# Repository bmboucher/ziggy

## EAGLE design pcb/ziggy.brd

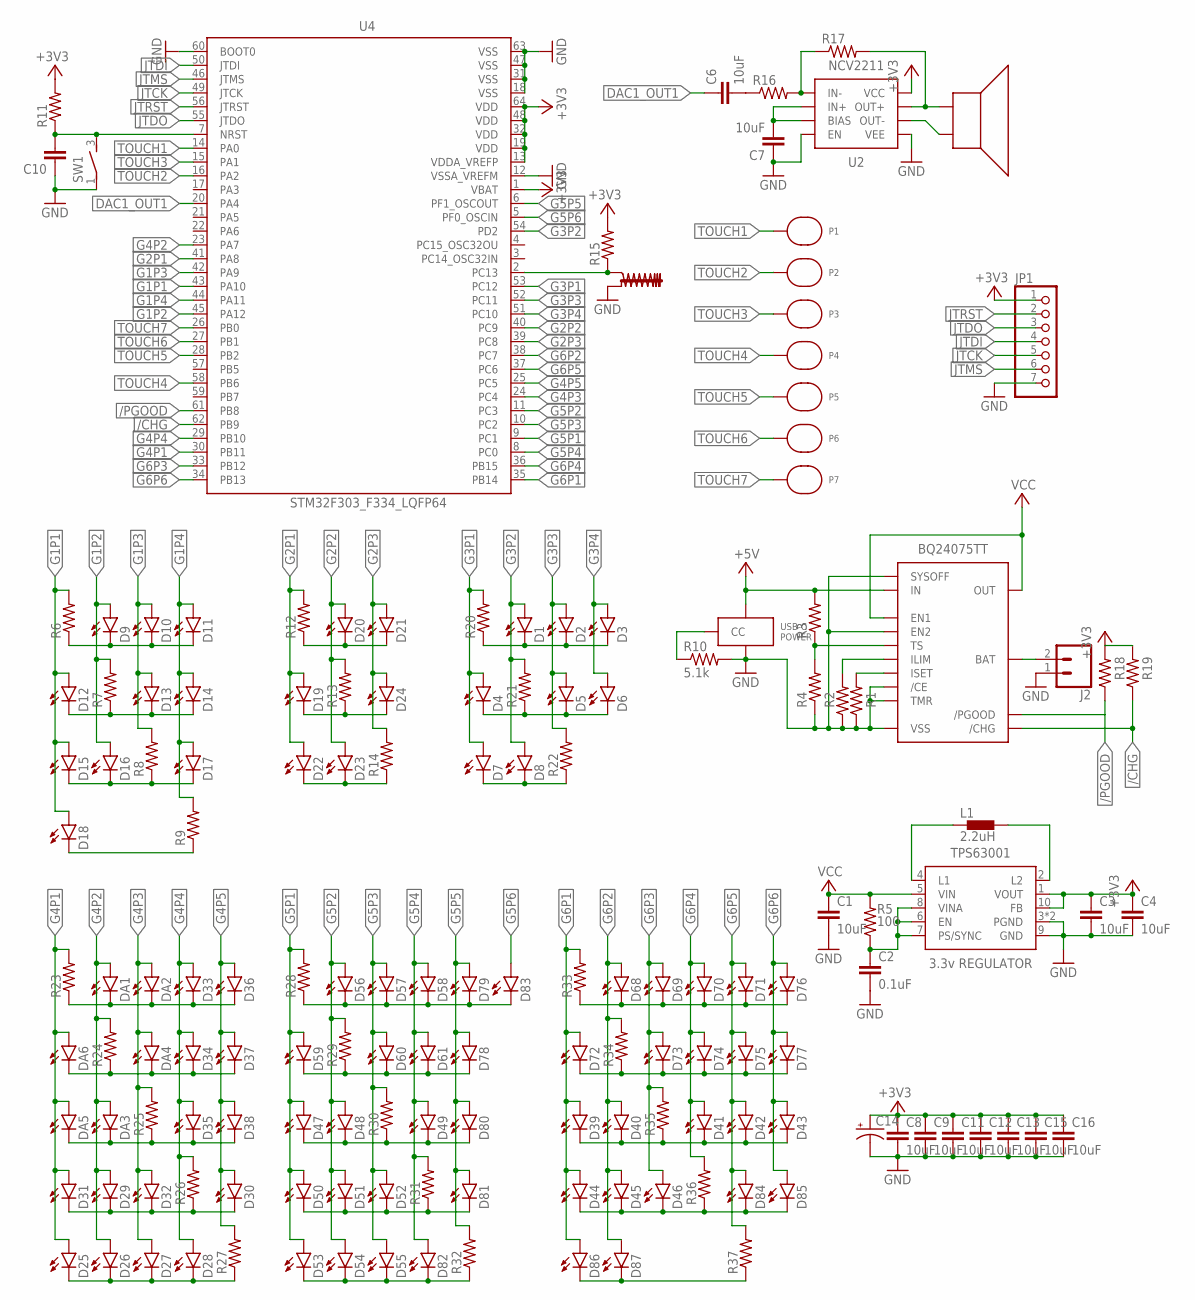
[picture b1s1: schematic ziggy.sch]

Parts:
C1, C3, C4, C6, C7, C8, C9, C11, C12, C13, C15, C16: 10uF; C0805
C2: 0.1uF; C0805
C10: C-EUC0805; C0805
C14: CPOL-US153CLV-0810; 153CLV-0810
D1, D2, D3, D4, D5, D6, D7, D8, D9, D10, D11, D12, D13, D14, D15, D16, D17, D18, D19, D20, D21, D22, D23, D24, D25, D26, D27, D28, D29, D30, D31, D32, D33, D34, D35, D36, D37, D38, D39, D40, D41, D42, D43, D44, D45, D46, D47, D48, D49, D50, D51, D52, D53, D54, D55, D56, D57, D58, D59, D60, D61, D68, D69, D70, D71, D72, D73, D74, D75, D76, D77, D78, D79, D80, D81, D82, D83, D84, D85, D86, D87: LED-0805; CHIPLED_0805
DA1, DA2, DA3, DA4, DA5, DA6: LED-0805; CHIPLED_0805
J1: USB-C-POWER; USB-C
J2: CONN_02-JST-2MM-SMT; JST-2-SMD
JP1: PINHD-1X7/90; 1X07/90
L1: 2.2uH; LPS3015
P1, P2, P3, P4, P5, P6, P7: CAPTOUCH
R1, R2, R3, R4, R6, R7, R8, R9, R11, R12, R13, R14, R15, R16, R17, R18, R19, R20, R21, R22, R23, R24, R25, R26, R27, R28, R29, R30, R31, R32, R33, R34, R35, R36, R37: R-US_R0805; R0805
R5: 100; R0805
R10: 5.1k; R0805
SP1: CMS-151103-088SP; CMS-151103
SW1: AS11CH
SW2: ADAFRUIT1767
U1: BQ24075TT; QFN50P300X300X100-17T168N
U2: NCV2211; SOIC127P600X175-8N
U3: TPS63001; SON50P300X300X100-11T165X240N
U4: STM32F303_F334_LQFP64; LQFP64_PACKAGE

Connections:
+3V3: C3.1, C4.1, C8.1, C9.1, C11.1, C12.1, C13.1, C14.+, C15.1, C16.1, JP1.1, R11.2, R15.2, R18.2, R19.2, U2.6 (VCC), U3.1 (VOUT), U3.10 (FB), U4.1 (VBAT), U4.13 (VDDA_VREFP), U4.19 (VDD), U4.32 (VDD), U4.48 (VDD), U4.64 (VDD)
+5V: J1.VBUS1 (VBUS), J1.VBUS2 (VBUS), R3.2, U1.13 (IN)
/CHG: R19.1, U1.9 (/CHG), U4.62 (PB9)
/PGOOD: R18.1, U1.7 (/PGOOD), U4.61 (PB8)
DAC1_OUT1: C6.1, U4.20 (PA4)
G1P1: D12.A, D15.A, D18.A, R6.2, U4.43 (PA10)
G1P2: D9.A, D16.A, R7.2, U4.45 (PA12)
G1P3: D10.A, D13.A, R8.2, U4.42 (PA9)
G1P4: D11.A, D14.A, D17.A, R9.2, U4.44 (PA11)
G2P1: D19.A, D22.A, R12.2, U4.41 (PA8)
G2P2: D20.A, D23.A, R13.2, U4.40 (PC9)
G2P3: D21.A, D24.A, R14.2, U4.39 (PC8)
G3P1: D4.A, D7.A, R20.2, U4.53 (PC12)
G3P2: D1.A, D8.A, R21.2, U4.54 (PD2)
G3P3: D2.A, D5.A, R22.2, U4.52 (PC11)
G3P4: D3.A, D6.A, U4.51 (PC10)
G4P1: D25.A, D31.A, DA5.A, DA6.A, R23.2, U4.30 (PB11)
G4P2: D26.A, D29.A, DA1.A, DA3.A, R24.2, U4.23 (PA7)
G4P3: D27.A, D32.A, DA2.A, DA4.A, R25.2, U4.24 (PC4)
G4P4: D28.A, D33.A, D34.A, D35.A, R26.2, U4.29 (PB10)
G4P5: D30.A, D36.A, D37.A, D38.A, R27.2, U4.25 (PC5)
G5P1: D47.A, D50.A, D53.A, D59.A, R28.2, U4.9 (PC1)
G5P2: D48.A, D51.A, D54.A, D56.A, R29.2, U4.11 (PC3)
G5P3: D52.A, D55.A, D57.A, D60.A, R30.2, U4.10 (PC2)
G5P4: D49.A, D58.A, D61.A, D82.A, R31.2, U4.8 (PC0)
G5P5: D78.A, D79.A, D80.A, D81.A, R32.2, U4.6 (PF1_OSCOUT)
G5P6: D83.A, U4.5 (PF0_OSCIN)
G6P1: D39.A, D44.A, D72.A, D86.A, R33.2, U4.35 (PB14)
G6P2: D40.A, D45.A, D68.A, D87.A, R34.2, U4.38 (PC7)
G6P3: D46.A, D69.A, D73.A, R35.2, U4.33 (PB12)
G6P4: D41.A, D70.A, D74.A, R36.2, U4.36 (PB15)
G6P5: D42.A, D71.A, D75.A, D84.A, R37.2, U4.37 (PC6)
G6P6: D43.A, D76.A, D77.A, D85.A, U4.34 (PB13)
GND: C1.2, C2.2, C3.2, C4.2, C7.1, C8.2, C9.2, C10.1, C11.2, C12.2, C13.2, C14.-, C15.2, C16.2, J1.GND1 (GND), J1.GND2 (GND), J2.1 (2), JP1.7, R1.1, R2.1, R4.1, R10.2, SW1.1, SW2.2, U1.4 (/CE), U1.5 (EN2), U1.8 (VSS), U1.14 (TMR), U1.15 (SYSOFF), U1.17 (VSS), U2.1 (EN), U2.7 (VEE), U3.3 (PGND), U3.9 (GND), U3.11 (PGND), U4.12 (VSSA_VREFM), U4.18 (VSS), U4.31 (VSS), U4.47 (VSS), U4.60 (BOOT0), U4.63 (VSS)
JTCK: JP1.5, U4.49 (JTCK)
JTDI: JP1.4, U4.50 (JTDI)
JTDO: JP1.3, U4.55 (JTDO)
JTMS: JP1.6, U4.46 (JTMS)
JTRST: JP1.2, U4.56 (JTRST)
unnamed: R1.2, U1.16 (ISET)
unnamed: R2.2, U1.12 (ILIM)
unnamed: J2.2 (1), U1.2 (BAT), U1.3 (BAT)
unnamed: R3.1, R4.2, U1.1 (TS)
unnamed: L1.1, U3.4 (L1)
unnamed: L1.2, U3.2 (L2)
unnamed: C2.1, R5.1, U3.6 (EN), U3.7 (PS/SYNC), U3.8 (VINA)
unnamed: D9.C, D10.C, D11.C, R6.1
unnamed: D12.C, D13.C, D14.C, R7.1
unnamed: D15.C, D16.C, D17.C, R8.1
unnamed: D18.C, R9.1
unnamed: J1.CC1 (CC), J1.CC2 (CC), R10.1
unnamed: D20.C, D21.C, R12.1
unnamed: D19.C, D24.C, R13.1
unnamed: D22.C, D23.C, R14.1
unnamed: R16.2, R17.1, U2.4 (IN-)
unnamed: C6.2, R16.1
unnamed: C7.2, U2.2 (BIAS), U2.3 (IN+)
unnamed: D7.C, D8.C, R22.1
unnamed: R17.2, SP1.2, U2.5 (OUT+)
unnamed: D4.C, D5.C, D6.C, R21.1
unnamed: D1.C, D2.C, D3.C, R20.1
unnamed: SP1.1, U2.8 (OUT-)
unnamed: D33.C, D36.C, DA1.C, DA2.C, R23.1
unnamed: D34.C, D37.C, DA4.C, DA6.C, R24.1
unnamed: D35.C, D38.C, DA3.C, DA5.C, R25.1
unnamed: D29.C, D30.C, D31.C, D32.C, R26.1
unnamed: D25.C, D26.C, D27.C, D28.C, R27.1
unnamed: D56.C, D57.C, D58.C, D79.C, D83.C, R28.1
unnamed: D59.C, D60.C, D61.C, D78.C, R29.1
unnamed: D47.C, D48.C, D49.C, D80.C, R30.1
unnamed: D50.C, D51.C, D52.C, D81.C, R31.1
unnamed: D53.C, D54.C, D55.C, D82.C, R32.1
unnamed: D68.C, D69.C, D70.C, D71.C, D76.C, R33.1
unnamed: D72.C, D73.C, D74.C, D75.C, D77.C, R34.1
unnamed: D39.C, D40.C, D41.C, D42.C, D43.C, R35.1
unnamed: D44.C, D45.C, D46.C, D84.C, D85.C, R36.1
unnamed: D86.C, D87.C, R37.1
NRST: C10.2, R11.1, SW1.3 (S), U4.7 (NRST)
TOUCH1: P1.P$1, U4.14 (PA0)
TOUCH2: P2.P$1, U4.16 (PA2)
TOUCH3: P3.P$1, U4.15 (PA1)
TOUCH4: P4.P$1, U4.58 (PB6)
TOUCH5: P5.P$1, U4.28 (PB2)
TOUCH6: P6.P$1, U4.27 (PB1)
TOUCH7: P7.P$1, U4.26 (PB0)
VCC: C1.1, R5.2, U1.6 (EN1), U1.10 (OUT), U1.11 (OUT), U3.5 (VIN)
VIBR_SENS: R15.1, SW2.1, U4.2 (PC13)

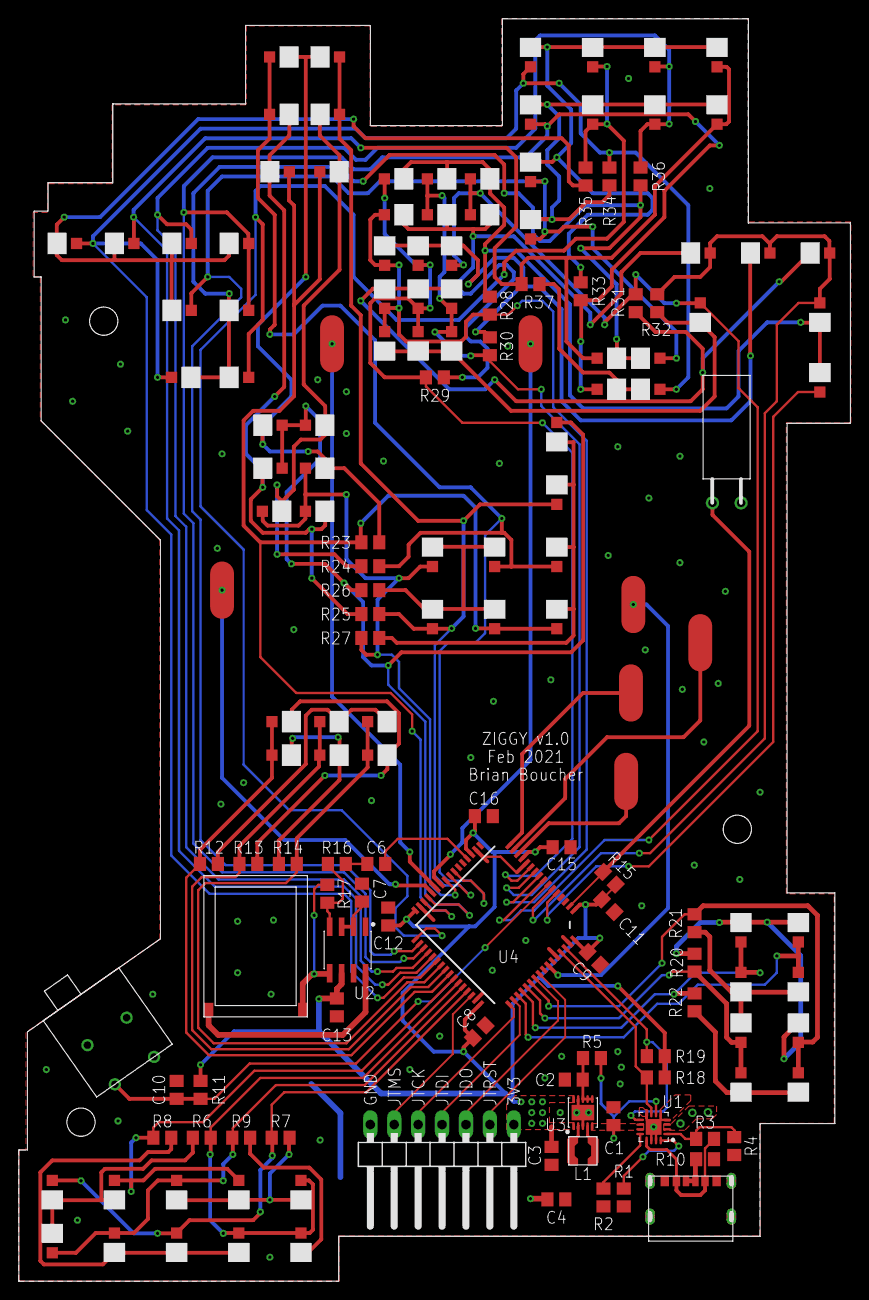
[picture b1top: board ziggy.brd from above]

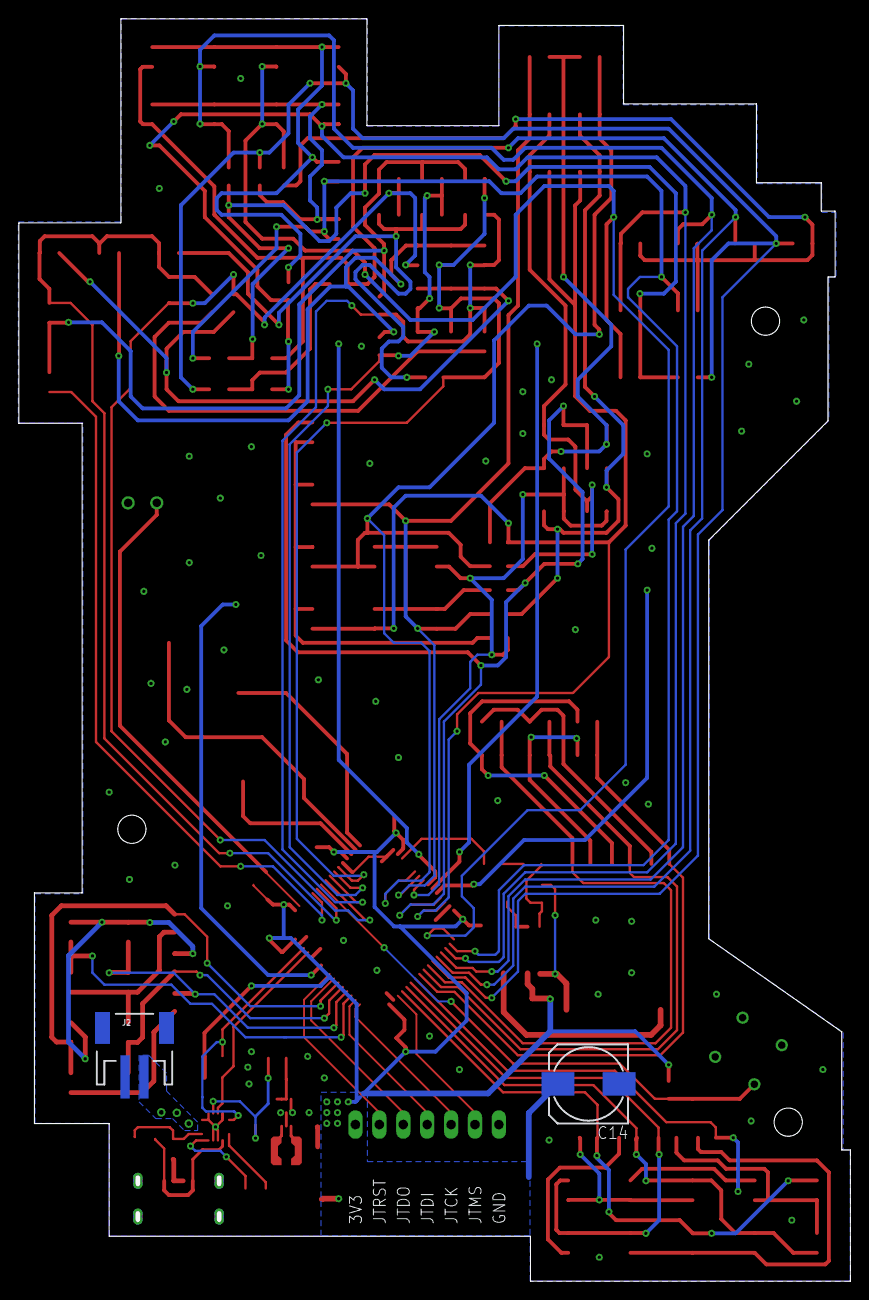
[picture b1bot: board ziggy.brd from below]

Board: 2 copper layers, 87.8 x 133.6 mm, 157 parts (2 on the bottom side), 87 nets.

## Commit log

2021-02-08 Initial board/schematic commit
2021-02-08 Adding cad subfolder

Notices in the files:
parts and their libraries:
SparkFun-Connectors: Licensing: Creative Commons ShareAlike 4.0 International - https://creativecommons.org/licenses/by-sa/4.0
